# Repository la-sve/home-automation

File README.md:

# home-automation

As I don't believe, this project is of much relevance to others, it is described in German only.
It is about my personal home automation using a lot of DS18S20 temperature sensors distributed in every room of my house to control my heating system via custom made DS2408 boards connected to some finder relays that switch the underfloor heating on and off for individual rooms.
Additionally, light switches (push buttons) are used as inputs to another part of the DS2408 boards, so that they can be used normally, apart from automation via _Home Assistant_. The latter is used for automation and as a user interface. Shutter control is also realized, but with custom boards using an i2c port expander (MCP23017).

**Kurzbeschreibung:** Projektdateien zur Automatisierung eines Hauses mittels Home Assistant, RaspPi und diversen Sensoren und Aktoren auf 1-Wire Basis.

## Dokumentation
Eine [Dokumentation](docs/index.md) findet sich im `docs`-Verzeichnis.

Ebenfalls erreichbar über [readthedocs](https://la-sve-home-automation.readthedocs.io/en/latest/).

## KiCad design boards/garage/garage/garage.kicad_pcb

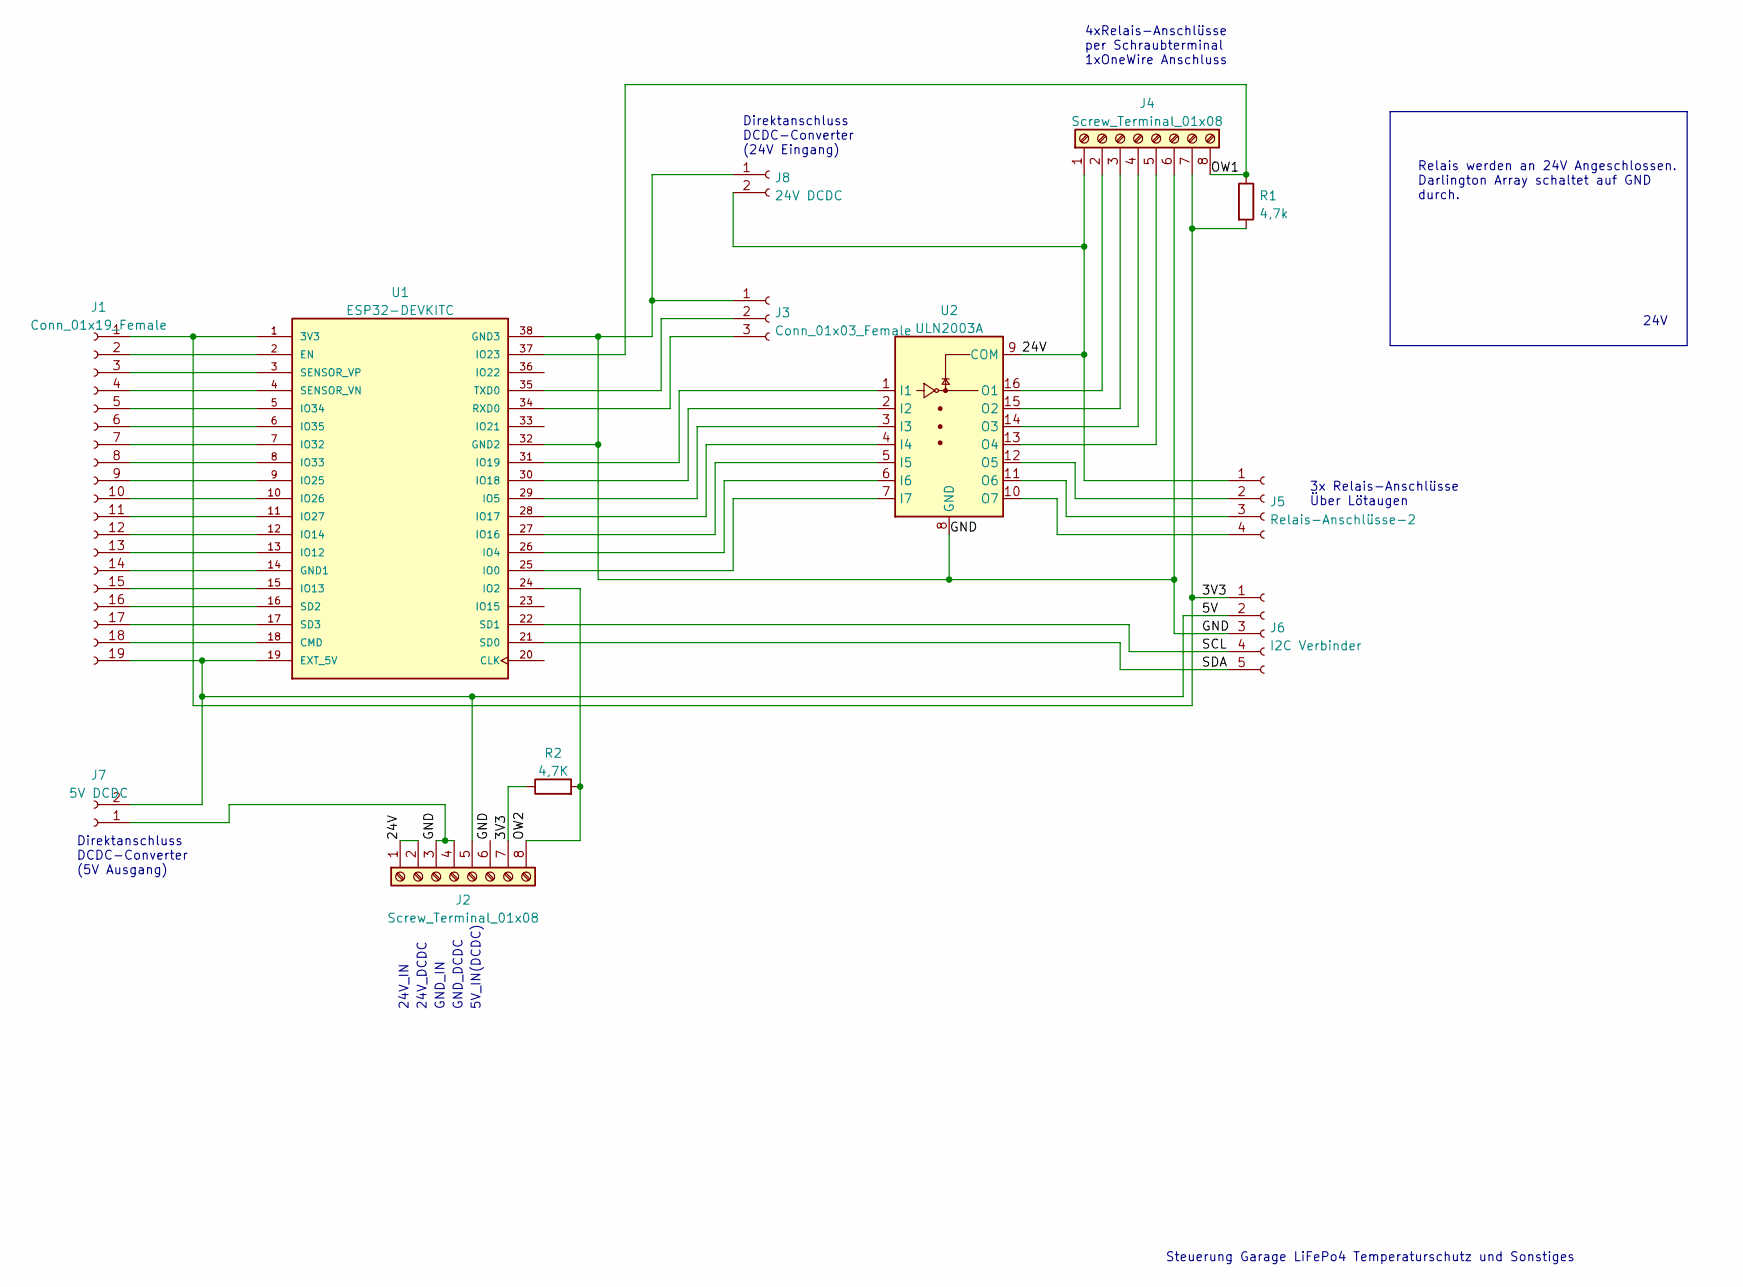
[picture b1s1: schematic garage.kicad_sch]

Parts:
J1: Conn_01x19_Female; PinSocket_1x19_P2.54mm_Vertical
J2, J4: Screw_Terminal_01x08; TerminalBlock_TE_282834-8_1x08_P2.54mm_Horizontal
J3: Conn_01x03_Female; PinSocket_1x03_P2.54mm_Vertical
J5: Relais-Anschlüsse-2; PinSocket_1x04_P2.54mm_Vertical
J6: I2C Verbinder; PinHeader_1x05_P2.54mm_Vertical
J7: 5V DCDC; PinHeader_1x02_P2.54mm_Vertical
J8: 24V DCDC; PinHeader_1x02_P2.54mm_Vertical
R1: 4,7k; R_Axial_DIN0309_L9.0mm_D3.2mm_P12.70mm_Horizontal
R2: 4,7K; R_Axial_DIN0309_L9.0mm_D3.2mm_P12.70mm_Horizontal
U1: ESP32-DEVKITC; MODULE_ESP32-DEVKITC; PARTREV N/A
U2: ULN2003A; DIP-16_W7.62mm

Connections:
/3V3: J1.1, J2.7, J4.7, J6.1, R1.2, R2.1, U1.1 (3V3)
/5V: J1.19, J2.5, J6.2, J7.2, U1.19 (EXT_5V)
/24V: J2.1, J2.2, J4.1, J5.1, J8.2, U2.9 (COM)
/GND: J2.3, J2.4, J2.6, J3.1, J4.6, J6.3, J7.1, J8.1, U1.32 (GND2), U1.38 (GND3), U2.8 (GND)
/OW1: J4.8, R1.1, U1.37 (IO23)
/OW2: J2.8, R2.2, U1.24 (IO2)
/SCL: J6.4, U1.22 (SD1)
/SDA: J6.5, U1.21 (SD0)
unnamed: J1.2, U1.2 (EN)
unnamed: J1.3, U1.3 (SENSOR_VP)
unnamed: J1.4, U1.4 (SENSOR_VN)
unnamed: J1.5, U1.5 (IO34)
unnamed: J1.6, U1.6 (IO35)
unnamed: J1.7, U1.7 (IO32)
unnamed: J1.8, U1.8 (IO33)
unnamed: J1.9, U1.9 (IO25)
unnamed: J1.10, U1.10 (IO26)
unnamed: J1.11, U1.11 (IO27)
unnamed: J1.12, U1.12 (IO14)
unnamed: J1.13, U1.13 (IO12)
unnamed: J1.14, U1.14 (GND1)
unnamed: J1.15, U1.15 (IO13)
unnamed: J1.16, U1.16 (SD2)
unnamed: J1.17, U1.17 (SD3)
unnamed: J1.18, U1.18 (CMD)
unnamed: J3.2, U1.35 (TXD0)
unnamed: J3.3, U1.34 (RXD0)
unnamed: J4.2, U2.16 (O1)
unnamed: J4.3, U2.15 (O2)
unnamed: J4.4, U2.14 (O3)
unnamed: J4.5, U2.13 (O4)
unnamed: J5.2, U2.12 (O5)
unnamed: J5.3, U2.11 (O6)
unnamed: J5.4, U2.10 (O7)
unnamed: U1.25 (IO0), U2.7 (I7)
unnamed: U1.26 (IO4), U2.6 (I6)
unnamed: U1.27 (IO16), U2.5 (I5)
unnamed: U1.28 (IO17), U2.4 (I4)
unnamed: U1.29 (IO5), U2.3 (I3)
unnamed: U1.30 (IO18), U2.2 (I2)
unnamed: U1.31 (IO19), U2.1 (I1)

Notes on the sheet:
Direktanschluss DCDC-Converter (5V Ausgang)
3x Relais-Anschlüsse Über Lötaugen
GND_IN
GND_DCDC
24V_DCDC
5V_IN(DCDC)
Steuerung Garage LiFePo4 Temperaturschutz und Sonstiges
Relais werden an 24V Angeschlossen. Darlington Array schaltet auf GND durch.
4xRelais-Anschlüsse per Schraubterminal 1xOneWire Anschluss
Direktanschluss DCDC-Converter (24V Eingang)
24V_IN
24V

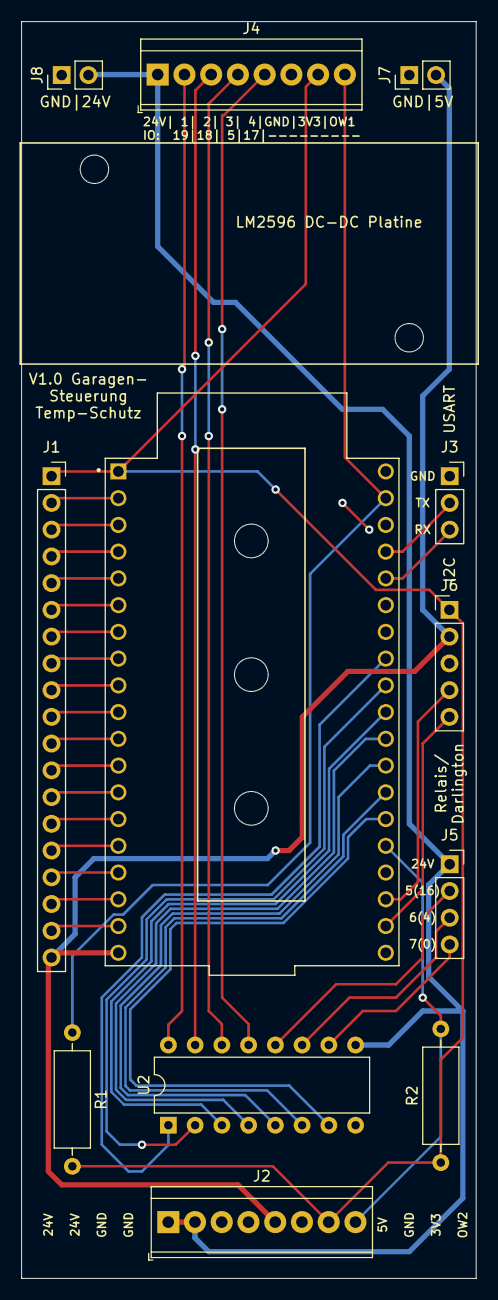
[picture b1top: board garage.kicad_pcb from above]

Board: 2 copper layers, 43.2 x 119.4 mm, 12 parts (0 on the bottom side), 41 nets.

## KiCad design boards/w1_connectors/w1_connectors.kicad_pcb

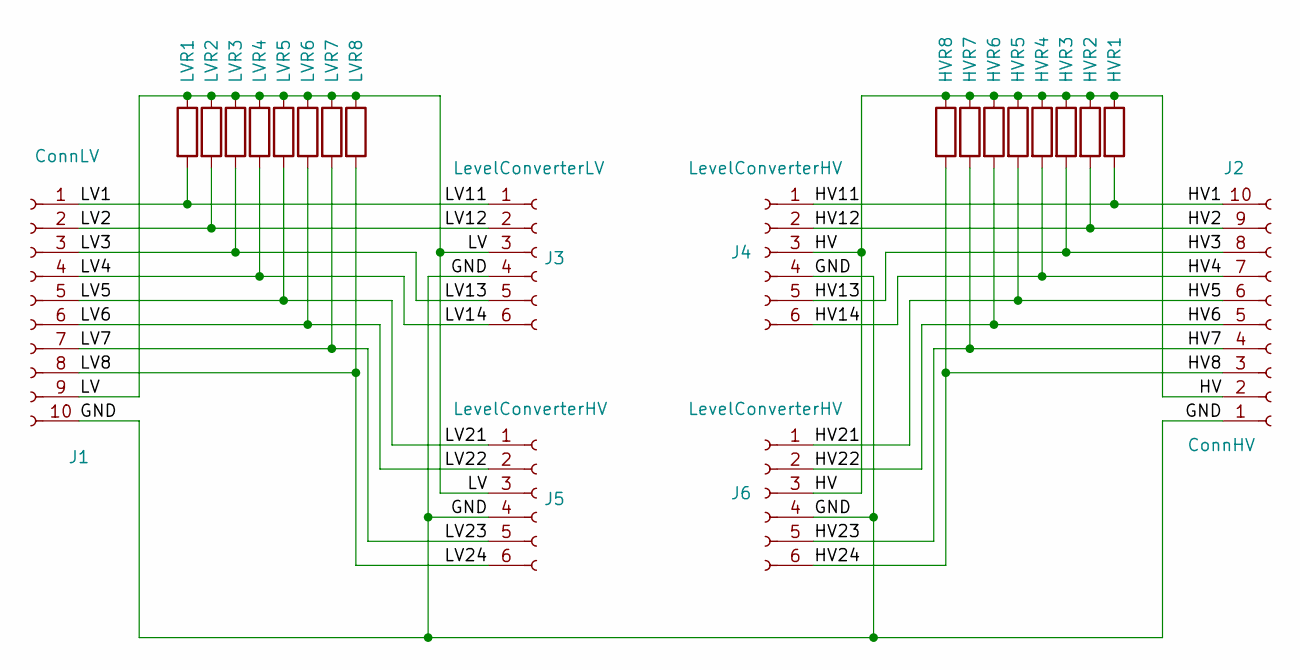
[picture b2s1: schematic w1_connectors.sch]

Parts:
HVR1, HVR2, HVR3, HVR4, HVR5, HVR6, HVR7, HVR8: R; R_1206_3216Metric_Pad1.30x1.75mm_HandSolder
J1: ConnLV; TerminalBlock_Phoenix_MPT-0,5-10-2.54_1x10_P2.54mm_Horizont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
J2: ConnHV; TerminalBlock_Phoenix_MPT-0,5-10-2.54_1x10_P2.54mm_Horizont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
J3: LevelConverterLV; PinSocket_1x06_P2.54mm_Vertical
J4, J5, J6: LevelConverterHV; PinSocket_1x06_P2.54mm_Vertical
LVR1, LVR2, LVR3, LVR4, LVR5, LVR6, LVR7, LVR8: R; R_1206_3216Metric_Pad1.30x1.75mm_HandSolder

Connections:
/GND: J1.10, J2.1, J3.4, J4.4, J5.4, J6.4
/HV: HVR1.1, HVR2.1, HVR3.1, HVR4.1, HVR5.1, HVR6.1, HVR7.1, HVR8.1, J2.2, J4.3, J6.3
/HV1: HVR1.2, J2.10, J4.1
/HV12: HVR2.2, J2.9, J4.2
/HV13: HVR3.2, J2.8, J4.5
/HV14: HVR4.2, J2.7, J4.6
/HV21: HVR5.2, J2.6, J6.1
/HV22: HVR6.2, J2.5, J6.2
/HV23: HVR7.2, J2.4, J6.5
/HV24: HVR8.2, J2.3, J6.6
/LV: J1.9, J3.3, J5.3, LVR1.1, LVR2.1, LVR3.1, LVR4.1, LVR5.1, LVR6.1, LVR7.1, LVR8.1
/LV1: J1.1, J3.1, LVR1.2
/LV12: J1.2, J3.2, LVR2.2
/LV13: J1.3, J3.5, LVR3.2
/LV14: J1.4, J3.6, LVR4.2
/LV21: J1.5, J5.1, LVR5.2
/LV22: J1.6, J5.2, LVR6.2
/LV23: J1.7, J5.5, LVR7.2
/LV24: J1.8, J5.6, LVR8.2

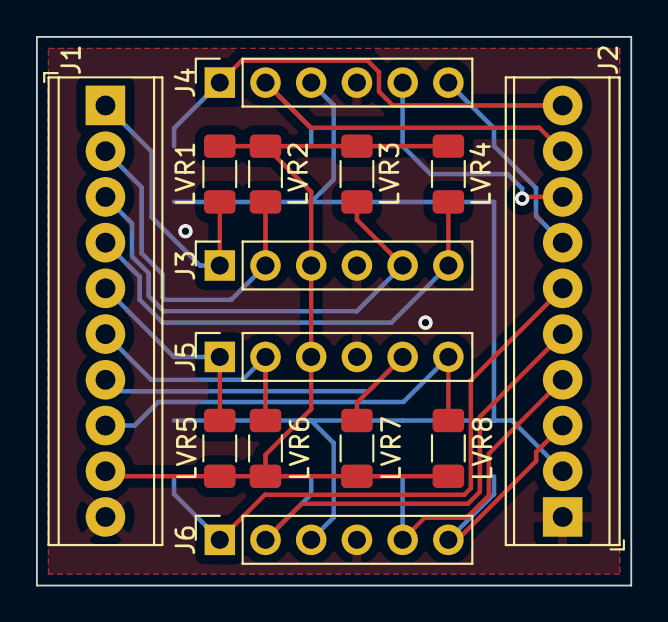
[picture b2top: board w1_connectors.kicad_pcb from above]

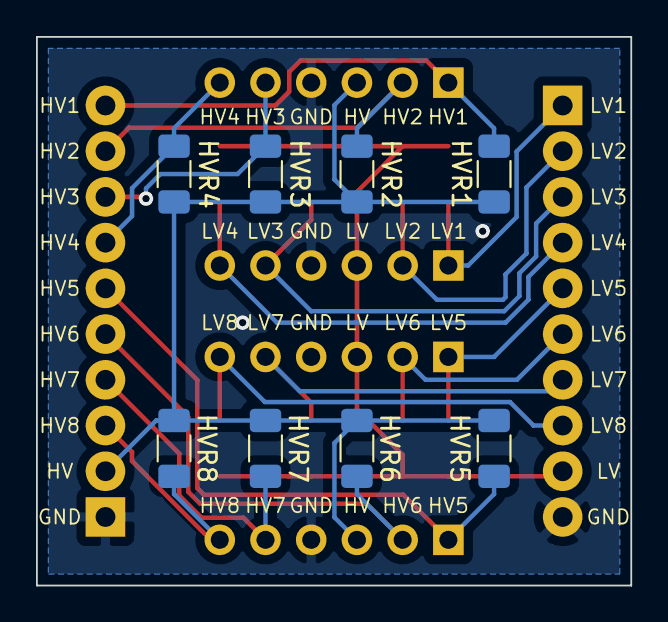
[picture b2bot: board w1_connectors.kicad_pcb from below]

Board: 2 copper layers, 33.0 x 30.5 mm, 22 parts (8 on the bottom side), 19 nets.

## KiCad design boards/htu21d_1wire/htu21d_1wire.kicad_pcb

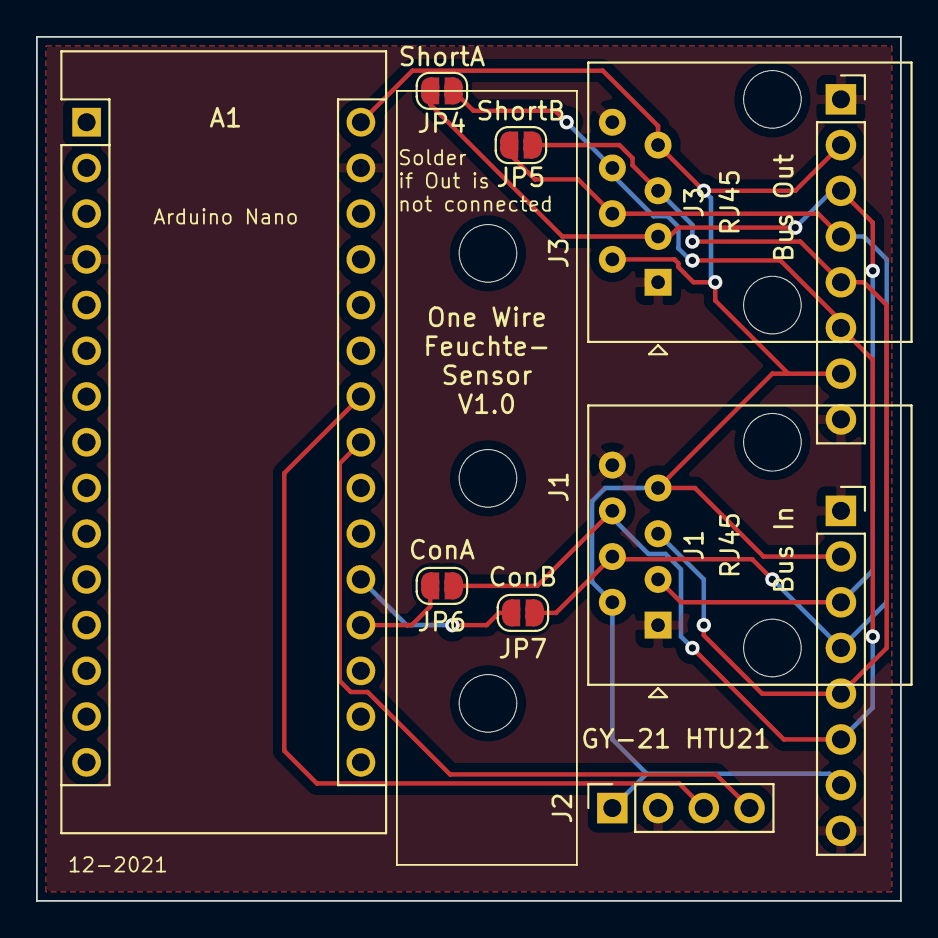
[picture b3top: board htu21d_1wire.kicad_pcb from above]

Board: 2 copper layers, 48.0 x 48.0 mm, 13 parts (0 on the bottom side), 10 nets.

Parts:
A1: Arduino_Nano_v2.x; Arduino_Nano
H1, H2, H3: MountingHole; MountingHole_3.2mm_M3
J1, J3: RJ45; RJ45_Amphenol_54602-x08_Horizontal
J2: GY-21 HTU21; PinSocket_1x04_P2.54mm_Vertical
J11: Bus In; PinSocket_1x08_P2.54mm_Vertical
J33: Bus Out; PinSocket_1x08_P2.54mm_Vertical
JP4: ShortA; SolderJumper-2_P1.3mm_Open_RoundedPad1.0x1.5mm
JP5: ShortB; SolderJumper-2_P1.3mm_Open_RoundedPad1.0x1.5mm
JP6: ConA; SolderJumper-2_P1.3mm_Open_RoundedPad1.0x1.5mm
JP7: ConB; SolderJumper-2_P1.3mm_Open_RoundedPad1.0x1.5mm

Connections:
/1Wire-A: A1.19, JP6.1
/1Wire-B: A1.20, JP7.2
/2A-5V: A1.30, J1.2, J1.7, J2.1, J3.2, J3.7, J11.2, J11.7, J33.2, J33.7
/2A-GND: A1.4, A1.29, J1.1, J1.8, J2.2, J3.1, J3.8, J11.1, J11.8, J33.1, J33.8
/2A-WireRueck: J1.3, J3.3, J11.3, J33.3, JP4.2
/2A-WireSensor: J1.6, J3.6, J11.6, J33.6, JP4.1, JP6.2
/2B-WireRueck: J1.5, J3.5, J11.5, J33.5, JP5.1
/2B-WireSensor: J1.4, J3.4, J11.4, J33.4, JP5.2, JP7.1
/SCL: A1.24, J2.3
/SDA: A1.23, J2.4

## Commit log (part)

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2021-09-28 First version of relais toggler
2021-09-29 Beschreibung aktualisiert
2021-10-01 hass config via git einrichten
2021-10-01 test, einchecken von configuration.yaml
2021-10-01 View Konfiguration hinzugefuegt
2021-10-02 Automatisierung auf Gruppe geaendert
2021-10-06 vicare hinzugefuegt
2021-10-07 Initialisieren der Dokumentation
2021-10-07 github freundliche Ansicht der Doku
2021-10-08 Bash aliases hinzugefuegt
2021-10-08 Dokumentation erweitert
2021-10-08 Weitere Doku uebernommen
2021-10-13 Weiter an Dokumentation gearbeitet
2021-10-16 Neue DS2408 Module in Betrieb genommen
2021-10-19 Doku erweitert
2021-11-03 Erste Arbeiten am Rollo-Modul
2021-11-09 Erste Testversion mit REST-Interface
2021-11-09 Rollo-Laufzeit einstellbar
2021-11-09 Rollo-Integrationstest
2021-11-10 Restrukturierung
2021-11-10 service einrichten und setup
2021-11-17 Rollos eingebunden
2021-11-18 Skript fuer Rollos OG hinzugefuegt
2021-11-20 Hinweis auf owhttpd service
2021-11-29 One Wire Feuchtesensor Code
2021-11-29 Update Konfiguration, Weihnachtslichter
2021-11-29 Doku Update DS2438
2021-11-29 Doku update
2021-12-13 htu21d board layout added
2021-12-13 kleine Ergänzungen
2021-12-14 kleinere Modifikationen
2021-12-19 Feuchtesensor uebertraegt erst nach erster Messung
2021-12-19 readthedocs integriert
2021-12-19 aliases fuer rollo control hinzugefuegt
2021-12-21 Schaltung Level Shifter fuer 8 one Wire Busleitungen
2021-12-25 Update hass und hwra sensor
2021-12-27 Doku verbessert
2022-01-07 Experimente mit ESPHome
2022-03-04 ESPHome yaml fuer Hydroponisches System.
2022-03-12 Initialisieren der Einstellungsdatei fuer die Poolsteuerung
2022-03-29 Pool-Steuerung und Hydroponisches System
2022-03-29 Aufraeumen
2022-04-10 HASS Konfiguration aktualisiert
2022-07-05 Einige Aenderungen
2022-07-05 Kompfort-AliasesÄ
2022-07-08 Testen von statistischen Auswertungen mit Jupyter Lab und SQLite Anbindung
2022-07-12 Hinweis auf interaktive Grafiken und Dockerfile hinzugefuegt
2022-07-13 Auswertung Strommessung
2022-07-28 jupyter notebooks noch etwas generalisiert
2022-12-10 Gruppen aktualisiert
2022-12-15 home assistant als docker
2022-12-16 onewire als volume hinzugefuegt
2022-12-16 Doku erweitert und cts700 modbus interface angefangen
2022-12-18 Versuch Verbindung von ESP32 zu CTS700 aufzubauen gescheitert. Jetzt per LAN
2022-12-18 Doku Lueftung
2022-12-18 Lueftungssteuerung hinzugefuegt
2023-01-01 Garagen-Board
2023-01-02 Neue Enditaeten
2023-01-03 Vorbereitung fuer Emporia Vue
2023-01-05 Batterieeintrag/austrag fuer energy dashboard
2023-01-08 Temperaturregelung Garage hinzugefuegt
2023-01-28 update auf neue SD Karte
2023-01-28 Doku Einrichten Raspi aktualisiert
2023-01-30 Auswertung Langzeitstatistik Home Assistant
2023-01-31 Statistik mit DWD Daten
2023-02-02 readthedocs reparieren
2023-03-31 Neue Steuereinheit
2023-09-03 luefter bei Hydro hinzugefuegt
2023-09-03 Pflanzlicht und solar ueberarbeitet
2024-12-26 Konfigurationsupdate
2024-12-26 neue HA Version
2024-12-29 vicare korrigiert
2025-08-04 Aktualisierte Konfigruation fuer HA auf ha.local
2025-09-04 Update auf neue HA-Version
